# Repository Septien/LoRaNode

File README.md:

A LoRa node that gathers data from sensors and uses a RFM to send the data to 
a master node.

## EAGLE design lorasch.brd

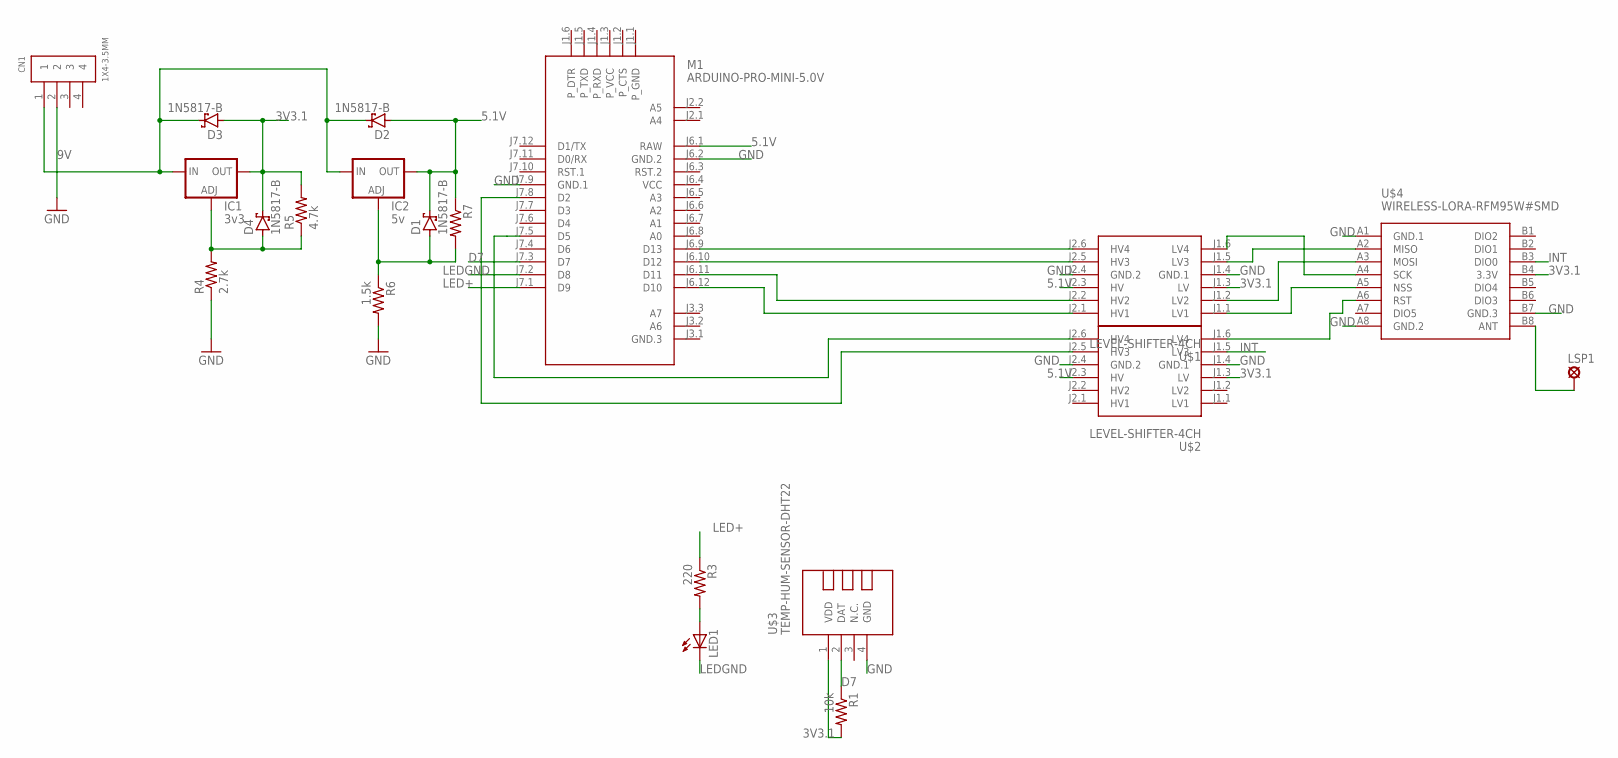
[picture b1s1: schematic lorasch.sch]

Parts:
CN1: 1X4-3.5MM; 1X04-3.5MM
D1, D2, D3, D4: 1N5817-B; DO41-7.6
IC1: 3v3; 317TL
IC2: 5v; 317TL
LED1: LED5MM
LSP1: SE14
M1: ARDUINO-PRO-MINI-5.0V; ARDUINO-PRO-MINI
R1: 10k; 0204/7
R3: 220; 0204/7
R4: 2.7k; 0204/7
R5: 4.7k; 0204/7
R6: 1.5k; 0204/7
R7: R-US_0204/7; 0204/7
U$1, U$2: LEVEL-SHIFTER-4CH
U$3: TEMP-HUM-SENSOR-DHT22
U$4: WIRELESS-LORA-RFM95W#SMD

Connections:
3V3.1: D3.A, D4.C, IC1.2 (OUT), R1.2, R5.2, U$1.J1.3 (LV), U$2.J1.3 (LV), U$3.1 (VDD), U$4.B4 (3.3V)
5.1V: D1.C, D2.A, IC2.2 (OUT), M1.J6.1 (RAW), R7.1, U$1.J2.3 (HV), U$2.J2.3 (HV)
9V: CN1.1, D2.C, D3.C, IC1.3 (IN), IC2.3 (IN)
D7: M1.J7.3 (D7), R1.1, U$3.2 (DAT)
GND: CN1.2, M1.J6.2 (GND.2), M1.J7.9 (GND.1), R4.1, R6.2, U$1.J1.4 (GND.1), U$1.J2.4 (GND.2), U$2.J1.4 (GND.1), U$2.J2.4 (GND.2), U$3.4 (GND), U$4.A1 (GND.1), U$4.A8 (GND.2), U$4.B7 (GND.3)
INT: U$2.J1.5 (LV3), U$4.B3 (DIO0)
LED+: M1.J7.1 (D9), R3.1
LEDGND: LED1.K (C), M1.J7.2 (D8)
unnamed: D4.A, IC1.1 (ADJ), R4.2, R5.1
unnamed: LED1.A, R3.2
unnamed: M1.J6.10 (D12), U$1.J2.5 (HV3)
unnamed: M1.J6.11 (D11), U$1.J2.2 (HV2)
unnamed: D1.A, IC2.1 (ADJ), R6.1, R7.2
unnamed: M1.J6.12 (D10), U$1.J2.1 (HV1)
unnamed: M1.J7.5 (D5), U$2.J2.6 (HV4)
unnamed: M1.J7.8 (D2), U$2.J2.5 (HV3)
unnamed: LSP1.MP, U$4.B8 (ANT)
unnamed: U$1.J1.2 (LV2), U$4.A3 (MOSI)
unnamed: U$1.J1.5 (LV3), U$4.A2 (MISO)
unnamed: U$1.J1.6 (LV4), U$4.A4 (SCK)
unnamed: M1.J6.9 (D13), U$1.J2.6 (HV4)
unnamed: U$1.J1.1 (LV1), U$4.A5 (NSS)
unnamed: U$2.J1.6 (LV4), U$4.A6 (RST)
VCC: M1.J6.4 (VCC)

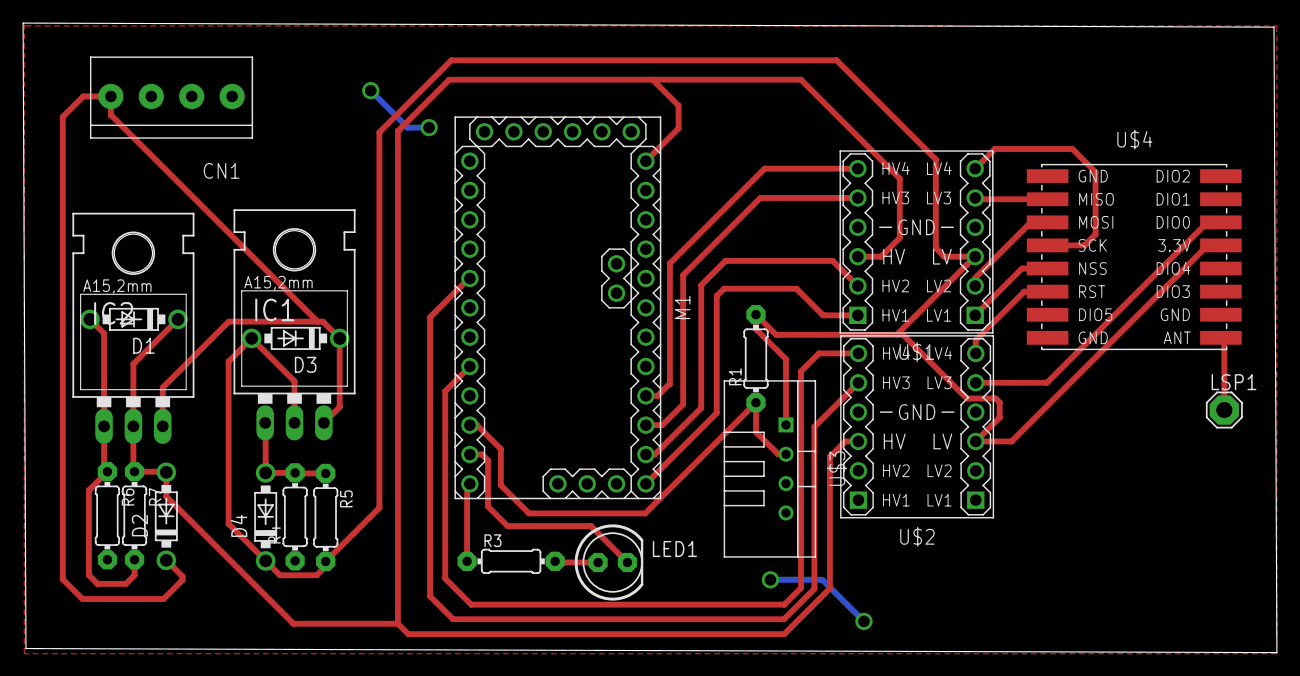
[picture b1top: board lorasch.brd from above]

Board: 2 copper layers, 108.5 x 54.5 mm, 20 parts (0 on the bottom side), 23 nets.

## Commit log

2020-05-13 First commit.
2020-05-13 Add lora node schematics.
2020-05-13 Add schematics.
2020-08-11 Modify schematic to reduce size of board.
2020-10-12 Add production schematic.
2020-10-12 Connect all grounds to common plane.
2020-10-21 Add production schematics.
2020-10-21 Change size of board.
2020-10-29 Add arduino pro mini 5v.
2021-01-11 Add change.

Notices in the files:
parts and their libraries:
dht22: Released under the Creative Commons Attribution 4.0 International License: http://creativecommons.org/licenses/by/4.0
